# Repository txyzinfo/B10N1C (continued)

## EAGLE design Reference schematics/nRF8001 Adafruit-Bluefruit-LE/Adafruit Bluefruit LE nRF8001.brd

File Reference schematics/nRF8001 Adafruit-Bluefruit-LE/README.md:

Adafruit-Bluefruit-LE-nRF8001-PCB
=================================

These are the PCB files for Adafruit Bluefruit LE nRF8001 PCB
Format is EagleCAD schematic and board layout

For more details, check out the product page at

-----> https://www.adafruit.com/product/1697

Adafruit invests time and resources providing this open source design, 
please support Adafruit and open-source hardware by purchasing 
products from Adafruit!

Designed by Adafruit Industries.  
Creative Commons Attribution, Share-Alike license, check license.txt for more information
All text above must be included in any redistribution

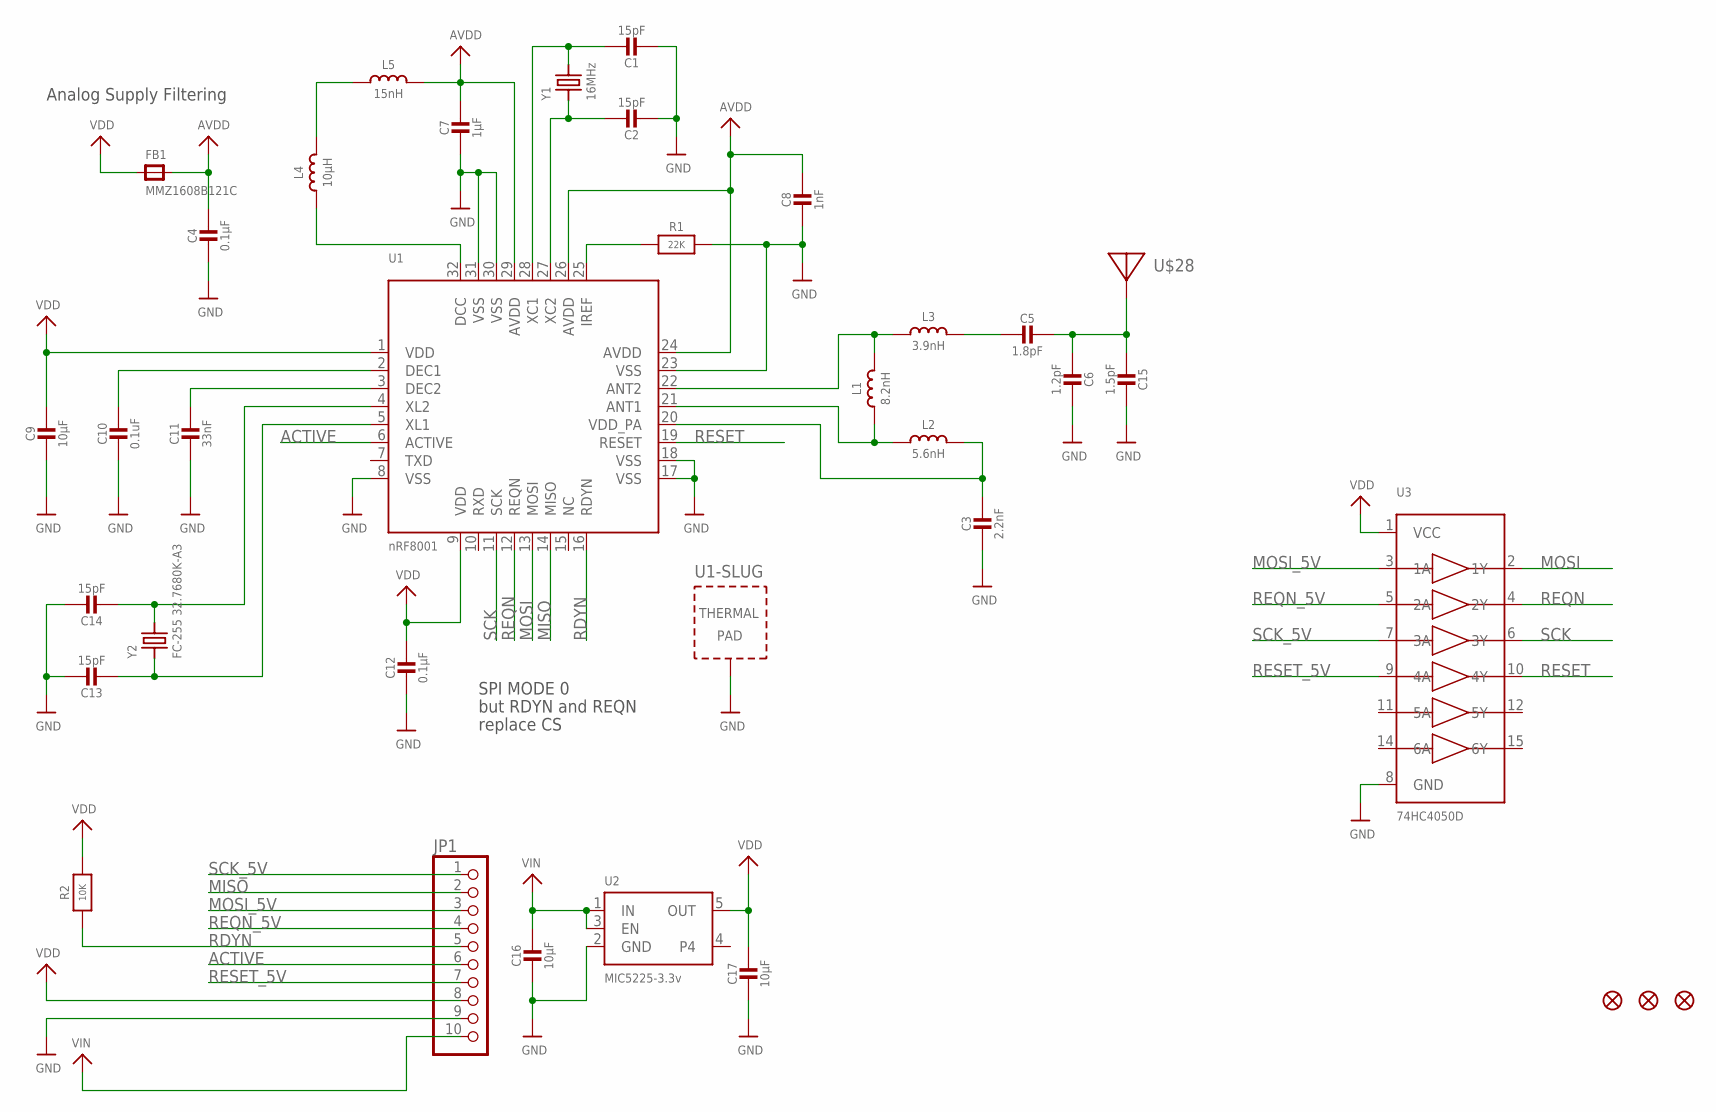
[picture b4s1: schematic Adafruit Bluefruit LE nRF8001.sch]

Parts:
C1, C2, C13, C14: 15pF; 0805-NO
C3: 2.2nF; _0402
C4, C12: 0.1µF; 0805-NO
C5: 1.8pF; _0402MP
C6: 1.2pF; _0402MP
C7: 1µF; 0805-NO
C8: 1nF; _0603
C9, C16, C17: 10µF; 0805-NO
C10: 0.1uF; 0805-NO
C11: 33nF; 0805-NO
C15: 1.5pF; _0402MP
FB1: MMZ1608B121C; 0805
FID1, FID2, FID3: FIDUCIAL""; FIDUCIAL_1MM
JP1: HEADER-1X1070MIL; 1X10_ROUND70
L1: 8.2nH; _0402
L2: 5.6nH; _0402
L3: 3.9nH; _0402
L4: 10µH; _0603
L5: 15nH; _0603
R1: 22K; _0805MP
R2: 10K; 0805-NO
U1: nRF8001; QFN32_5MM
U2: MIC5225-3.3v; SOT23-5
U3: 74HC4050D; TSSOP16
U$28: ANTENNA_PCBNRF8001_1.6MM; ANT_PCB_2.4GHZ_NRF8001_1.6MM_1OZ
Y1: 16MHz; CRYSTAL_2.5X2
Y2: FC-255 32.7680K-A3; CRYSTAL_4.9X1.8

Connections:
ACTIVE: JP1.6, U1.6 (ACTIVE)
AVDD: C4.1, C7.1, C8.1, FB1.2, L5.2, U1.24 (AVDD), U1.26 (AVDD), U1.29 (AVDD)
GND: C1.2, C2.2, C3.2, C4.2, C6.1, C7.2, C8.2, C9.2, C10.2, C11.2, C12.2, C13.1, C14.1, C15.1, C16.2, C17.2, JP1.9, R1.2, U1.8 (VSS), U1.17 (VSS), U1.18 (VSS), U1.23 (VSS), U1.30 (VSS), U1.31 (VSS), U1.33 (TP), U2.2 (GND), U3.8 (GND)
MISO: JP1.2, U1.14 (MISO)
MOSI: U1.13 (MOSI), U3.2 (1Y)
MOSI_5V: JP1.3, U3.3 (1A)
unnamed: L1.2, L3.1, U1.22 (ANT2)
unnamed: L1.1, L2.1, U1.21 (ANT1)
unnamed: C3.1, L2.2, U1.20 (VDD_PA)
unnamed: L4.2, L5.1
unnamed: C5.2, L3.2
unnamed: C11.1, U1.3 (DEC2)
unnamed: C10.1, U1.2 (DEC1)
unnamed: C1.1, U1.28 (XC1), Y1.3 (2)
unnamed: C2.1, U1.27 (XC2), Y1.1
unnamed: L4.1, U1.32 (DCC)
unnamed: R1.1, U1.25 (IREF)
unnamed: C5.1, C6.2, C15.2, U$28.FEED
unnamed: C14.2, U1.4 (XL2), Y2.2
unnamed: C13.2, U1.5 (XL1), Y2.1
RDYN: JP1.5, R2.1, U1.16 (RDYN)
REQN: U1.12 (REQN), U3.4 (2Y)
REQN_5V: JP1.4, U3.5 (2A)
RESET: U1.19 (RESET), U3.10 (4Y)
RESET_5V: JP1.7, U3.9 (4A)
SCK: U1.11 (SCK), U3.6 (3Y)
SCK_5V: JP1.1, U3.7 (3A)
VDD: C9.1, C12.1, C17.1, FB1.1, JP1.8, R2.2, U1.1 (VDD), U1.9 (VDD), U2.5 (OUT), U3.1 (VCC)
VIN: C16.1, JP1.10, U2.1 (IN), U2.3 (EN)

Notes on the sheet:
Analog Supply Filtering
SPI MODE 0
but RDYN and REQN
replace CS

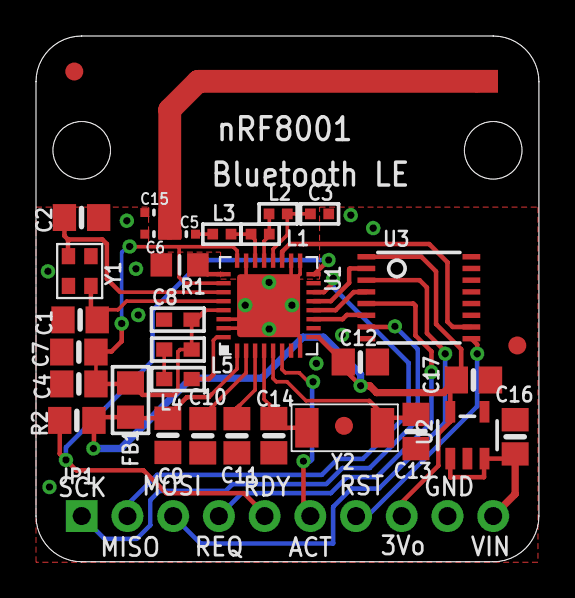
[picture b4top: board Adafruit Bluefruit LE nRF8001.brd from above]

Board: 2 copper layers, 27.9 x 29.2 mm, 36 parts (1 on the bottom side), 29 nets.

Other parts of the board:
U$22: ADAFRUIT_TEXT_20MM

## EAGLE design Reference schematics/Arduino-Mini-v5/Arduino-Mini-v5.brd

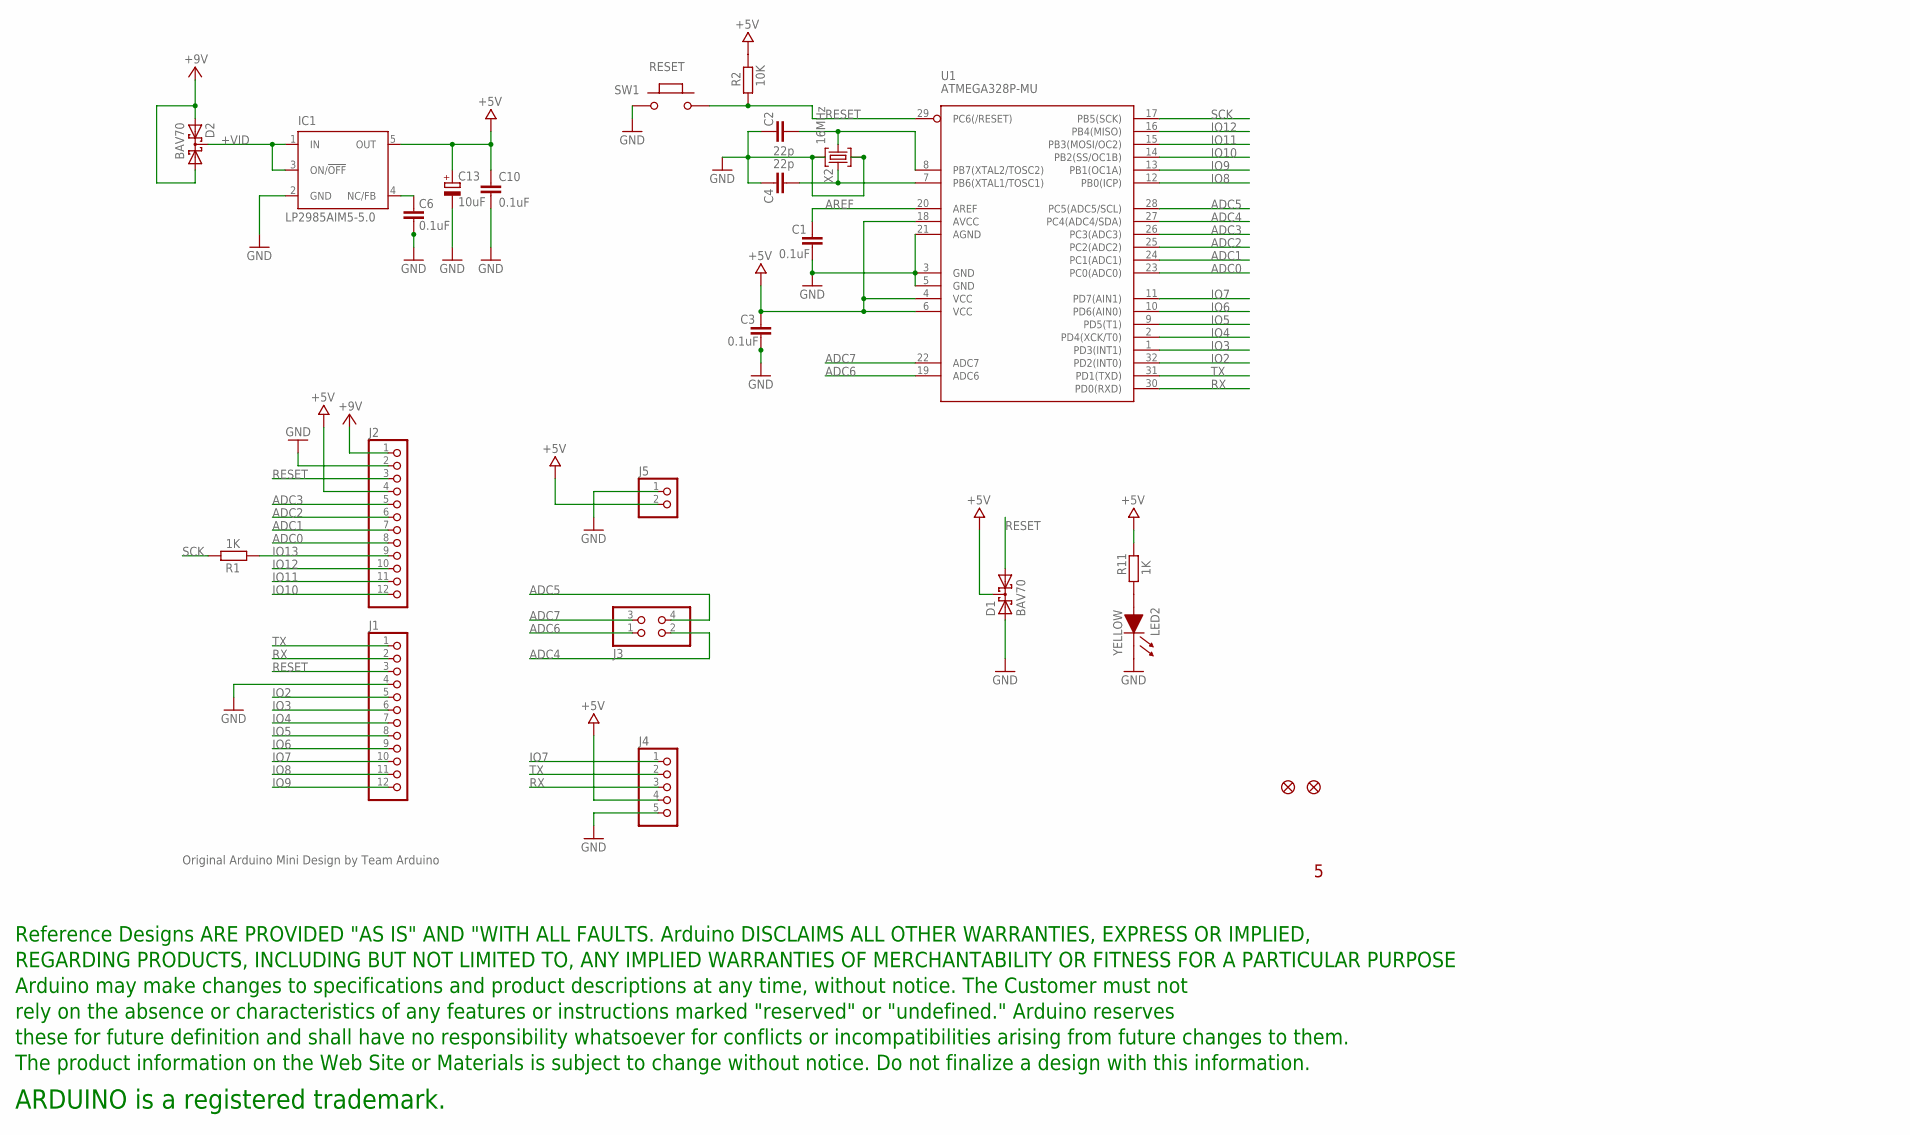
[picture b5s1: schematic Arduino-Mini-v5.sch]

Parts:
C1, C3, C6, C10: 0.1uF; C0603-ROUND
C2, C4: 22p; C0603-ROUND
C13: 10uF; SMC_B
D1, D2: BAV70; SOT23
IC1: LP2985AIM5-5.0; SOT23-DBV
J1, J2: PINHD-1X12; 1X12
J3: PINHD-2X2; 2X02
J4: PINHD-1X5; 1X5
J5: PINHD-1X2; 1X2
LED2: YELLOW; SMD_LED0805
R1, R11: 1K; R0603-ROUND
R2: 10K; R0603-ROUND
SW1: RESET; SMD_157SW
U1: ATMEGA328P-MU; MLF32-M1-A
U$2, U$4: FIDUCIAL1X2; FIDUCIAL-1X2
U$11: DISCLAIMER
X2: 16MHz; CRYSTAL-3.2-2.5

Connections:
+5V: C3.2, C10.1, C13.+, D1.3 (C), IC1.5 (OUT), J2.4, J4.4, J5.2, R2.2, R11.2, U1.4 (VCC), U1.6 (VCC), U1.18 (AVCC)
+VID: D2.3 (C), IC1.1 (IN), IC1.3 (ON/!OFF)
ADC0: J2.8, U1.23 (PC0(ADC0))
ADC1: J2.7, U1.24 (PC1(ADC1))
ADC2: J2.6, U1.25 (PC2(ADC2))
ADC3: J2.5, U1.26 (PC3(ADC3))
ADC4: J3.2, U1.27 (PC4(ADC4/SDA))
ADC5: J3.4, U1.28 (PC5(ADC5/SCL))
ADC6: J3.1, U1.19 (ADC6)
ADC7: J3.3, U1.22 (ADC7)
AREF: C1.2, U1.20 (AREF)
GND: C1.1, C2.2, C3.1, C4.2, C6.1, C10.2, C13.-, D1.1 (A1), IC1.2 (GND), J1.4, J2.2, J4.5, J5.1, LED2.1 (CA), SW1.1, U1.3 (GND), U1.5 (GND), U1.21 (AGND), X2.2 (GND), X2.4 (GND)
IO2: J1.5, U1.32 (PD2(INT0))
IO3: J1.6, U1.1 (PD3(INT1))
IO4: J1.7, U1.2 (PD4(XCK/T0))
IO5: J1.8, U1.9 (PD5(T1))
IO6: J1.9, U1.10 (PD6(AIN0))
IO7: J1.10, J4.1, U1.11 (PD7(AIN1))
IO8: J1.11, U1.12 (PB0(ICP))
IO9: J1.12, U1.13 (PB1(OC1A))
IO10: J2.12, U1.14 (PB2(SS/OC1B))
IO11: J2.11, U1.15 (PB3(MOSI/OC2))
IO12: J2.10, U1.16 (PB4(MISO))
IO13: J2.9, R1.1
unnamed: C4.1, U1.7 (PB6(XTAL1/TOSC1)), X2.1 (C1)
unnamed: C2.1, U1.8 (PB7(XTAL2/TOSC2)), X2.3 (C2)
unnamed: C6.2, IC1.4 (NC/FB)
unnamed: LED2.2 (AN), R11.1
RESET: D1.2 (A2), J1.3, J2.3, R2.1, SW1.2, U1.29 (PC6(/RESET))
RX: J1.2, J4.3, U1.30 (PD0(RXD))
SCK: R1.2, U1.17 (PB5(SCK))
TX: J1.1, J4.2, U1.31 (PD1(TXD))
VCC: D2.1 (A1), D2.2 (A2), J2.1

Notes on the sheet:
Original Arduino Mini Design by Team Arduino

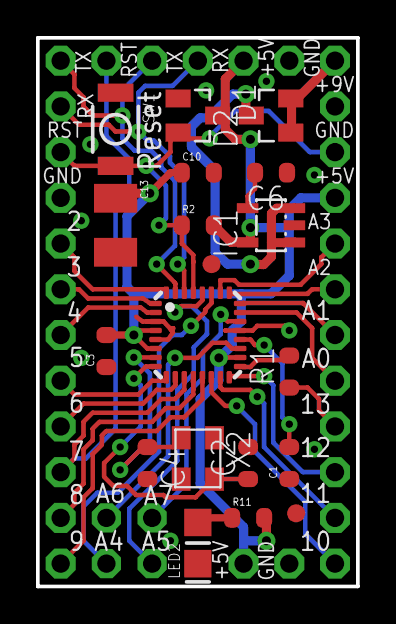
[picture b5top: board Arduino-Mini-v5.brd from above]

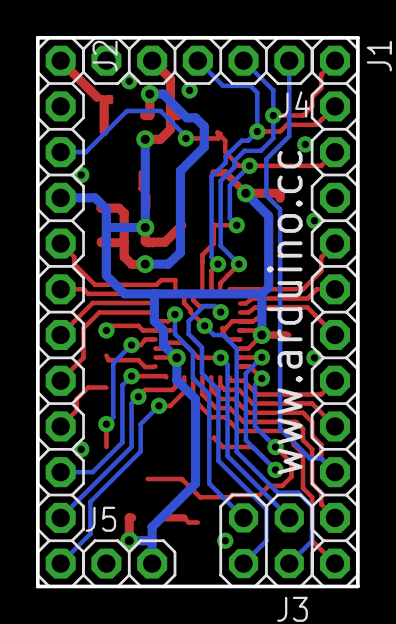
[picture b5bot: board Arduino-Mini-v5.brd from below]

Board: 2 copper layers, 17.8 x 30.5 mm, 25 parts (5 on the bottom side), 33 nets.

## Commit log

2014-08-20 :tada: Added .gitattributes & .gitignore files
2014-08-20 Revert ":tada: Added .gitattributes & .gitignore files"
    This reverts commit fcdb2b6727e0231f25f6e6821006f96a9919206c.
2014-08-20 Bionic
    first datasheets
2014-08-21 2
    2
2014-08-21 3
    3
2014-09-29 Arduino Code Update
2014-09-29 New mechanical design files
2014-10-05 new/updated datasheets
2014-10-11 more reference schemtics
2014-10-11 Revert "more reference schemtics"
    This reverts commit ba5c82df02fb927dbc1ffc3cdf36eef71b5405af.
2014-10-11 Revert "Revert "more reference schemtics""
    This reverts commit 6b1c06b5fb51e62de6375dfcb8688c407b875b8b.
2014-10-11 Reference schem 2
2014-10-11 hmm 2
2014-10-11 Reference schem 3
2014-10-12 Improvement for NRF8001 circuit
2014-10-13 NRF8001 schem+layout completed
2014-10-14 ATMEGA328 & PN532 circuit added to b10n1c schamtic
2014-10-25 PCB and Schem updated, new Eagle libs
2014-10-26 PN532 PCB layout completed
2014-12-28 bq51013A schematic added
2015-02-23 Power DONE!
    BQ51013 + LTC4065 + MCP1700 schematic and PCB layout DONE
2015-02-23 old and bkp files removed
